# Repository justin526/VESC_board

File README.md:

# VESC_board
Our custom ESC board designed by two wonderfully inexperienced Purdue students

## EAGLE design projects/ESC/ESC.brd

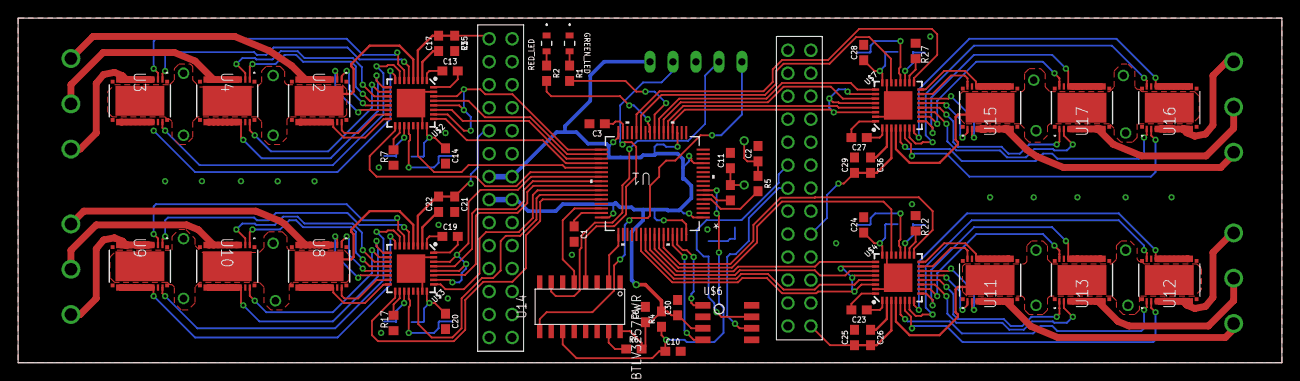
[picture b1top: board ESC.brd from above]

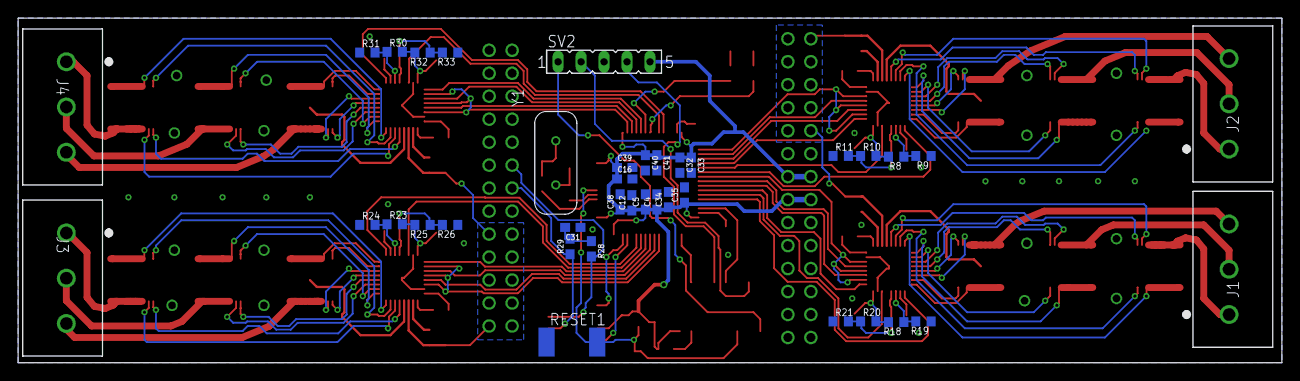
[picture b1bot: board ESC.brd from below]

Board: 4 copper layers, 139.7 x 38.1 mm, 93 parts (38 on the bottom side), 125 nets.

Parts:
C1, C3: 2.2uF; 0603
C2, C4, C5, C10, C11, C12, C16, C30, C32, C33, C34, C35, C38, C39, C40, C41: 4.7uF; 0603
C6, C15, C21, C25, C29, C31: 0.1uF; 0603
C13, C19, C23, C27: 47nF; 0603
C14, C17, C20, C22, C24, C26, C28, C36: 1.0uF; 0603
GREEN_LED: TLMS1100-GS08; LED_VISHAY_TLMX1100
J1, J2, J3, J4: 1755529; CONN_1755529
R1, R2, R3, R4, R5: 1k; 0603
R6: 1.5k; 0603
R7, R17, R22, R27: 47k; R0603
R8, R9, R10, R11, R18, R19, R20, R21, R23, R24, R25, R26, R30, R31, R32, R33: R0603
R28, R29: 60; 0603
RED_LED: TLMS1100-GS08; LED_VISHAY_TLMX1100
RESET1: SW_2512
SV2: FE05-1
U1: STM32F405RGT6; LQFP-64
U2, U3, U4, U8, U9, U10, U11, U12, U13, U15, U16, U17: CSD88584Q5DCT; DMM0022A
U14: SN74CBTLV3257PWR
U$2, U$3, U$4, U$7: DRV8320H; QFN-32-5X5MM
U$5: ESC2BACKPLANE; ESC2BACKPLANE_WHOLE
U$6: TCAN337D
Y1: ECS-80-S-4X; XTAL_ECS-80-S-4X

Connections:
+3V3: C4.1, C5.1, C6.1, C12.1, C16.1, C30.1, C32.1, C33.1, C34.1, C35.1, C38.1, C39.1, C40.1, C41.1, R4.2, R6.2, SV2.5, U1.1, U1.13, U1.19, U1.32, U1.48, U1.64, U14.P$16, U$5.P$G, U$5.P$H, U$5.P$U, U$5.P$V, U$6.VCC
+12V: C15.1, C17.2, C21.1, C22.2, C25.1, C26.2, C29.1, C36.2, U2.27, U3.27, U4.27, U8.27, U9.27, U10.27, U11.27, U12.27, U13.27, U15.27, U16.27, U17.27, U$2.3, U$2.4, U$3.3, U$3.4, U$4.3, U$4.4, U$5.P$9, U$5.P$10, U$5.P$11, U$5.P$12, U$5.P$13, U$5.P$23, U$5.P$24, U$5.P$25, U$5.P$26, U$5.P$27, U$5.P$A, U$5.P$B, U$5.P$C, U$5.P$D, U$5.P$E, U$5.P$O, U$5.P$P, U$5.P$Q, U$5.P$R, U$5.P$S, U$7.3, U$7.4
CAN_H: R28.2, U$5.P$6, U$6.CANH
CAN_L: R29.1, U$5.P$7, U$6.CANL
CAN_RX: U1.61, U$6.RXD
CAN_TX: U1.62, U$6.TXD
DVDD_1: C14.1, R8.2, R10.2, U$2.24
DVDD_2: C20.1, R18.2, R20.2, U$3.24
DVDD_3: C24.1, R23.2, R25.2, U$4.24
DVDD_4: C28.1, R30.2, R32.2, U$7.24
EN_1: U1.37, U$2.22
EN_2: U1.43, U$3.22
EN_3: U1.58, U$4.22
EN_4: U1.27, U$7.22
FAULT_1: U1.38, U$2.17
FAULT_2: U1.44, U$3.17
FAULT_3: U1.59, U$4.17
FAULT_4: U1.28, U$7.17
GHA_1: U3.1, U$2.5
GHA_2: U9.1, U$3.5
GHA_3: U12.1, U$4.5
GHA_4: U16.1, U$7.5
GHB_1: U4.1, U$2.12
GHB_2: U10.1, U$3.12
GHB_3: U13.1, U$4.12
GHB_4: U17.1, U$7.12
GHC_1: U2.1, U$2.13
GHC_2: U8.1, U$3.13
GHC_3: U11.1, U$4.13
GHC_4: U15.1, U$7.13
GLA_1: U3.22, U$2.7
GLA_2: U9.22, U$3.7
GLA_3: U12.22, U$4.7
GLA_4: U16.22, U$7.7
GLB_1: U4.22, U$2.10
GLB_2: U10.22, U$3.10
GLB_3: U13.22, U$4.10
GLB_4: U17.22, U$7.10
GLC_1: U2.22, U$2.15
GLC_2: U8.22, U$3.15
GLC_3: U11.22, U$4.15
GLC_4: U15.22, U$7.15
GND: C1.2, C2.2, C3.2, C4.2, C5.2, C6.2, C10.2, C11.2, C12.2, C14.2, C15.2, C16.2, C20.2, C21.2, C24.2, C25.2, C28.2, C29.2, C30.2, C31.1, C32.2, C33.2, C34.2, C35.2, C38.2, C39.2, C40.2, C41.2, GREEN_LED.1, R7.1, R9.1, R11.1, R17.1, R19.1, R21.1, R22.1, R24.1, R26.1, R27.1, R31.1, R33.1, RED_LED.1, RESET1.1, SV2.3, U1.12, U1.18, U1.60, U1.63, U2.12, U2.13, U2.14, U2.15, U2.16, U2.17, U2.18, U2.19, U2.20, U3.12, U3.13, U3.14, U3.15, U3.16, U3.17, U3.18, U3.19, U3.20, U4.12, U4.13, U4.14, U4.15, U4.16, U4.17, U4.18, U4.19, U4.20, U8.12, U8.13, U8.14, U8.15, U8.16, U8.17, U8.18, U8.19, U8.20, U9.12, U9.13, U9.14, U9.15, U9.16, U9.17, U9.18, U9.19, U9.20, U10.12, U10.13, U10.14, U10.15, U10.16, U10.17, U10.18, U10.19, U10.20, U11.12, U11.13, U11.14, U11.15, U11.16, U11.17, U11.18, U11.19, U11.20, U12.12, U12.13, U12.14, U12.15, U12.16, U12.17, U12.18, U12.19, U12.20, U13.12, U13.13, U13.14, U13.15, U13.16, U13.17, U13.18, U13.19, U13.20, U14.P$8, U15.12, U15.13, U15.14, U15.15, U15.16, U15.17, U15.18, U15.19, U15.20, U16.12, U16.13, U16.14, U16.15, U16.16, U16.17, U16.18, U16.19, U16.20, U17.12, U17.13, U17.14, U17.15, U17.16, U17.17, U17.18, U17.19, U17.20, U$2.8, U$2.9, U$2.16, U$2.23, U$2.31, U$2.EP, U$3.8, U$3.9, U$3.16, U$3.23, U$3.31, U$3.EP, U$4.8, U$4.9, U$4.16, U$4.23, U$4.31, U$4.EP, U$5.P$1, U$5.P$2, U$5.P$3, U$5.P$4, U$5.P$15, U$5.P$16, U$5.P$17, U$5.P$18, U$5.P$AA, U$5.P$BB, U$5.P$J, U$5.P$K, U$5.P$L, U$5.P$M, U$5.P$N, U$5.P$X, U$5.P$Y, U$5.P$Z, U$6.GND, U$7.8, U$7.9, U$7.16, U$7.23, U$7.31, U$7.EP
INHA_1: U1.36, U$2.25
INHA_2: U1.42, U$3.25
INHA_3: U1.57, U$4.25
INHA_4: U1.23, U$7.25
INHB_1: U1.35, U$2.27
INHB_2: U1.41, U$3.27
INHB_3: U1.56, U$4.27
INHB_4: U1.22, U$7.27
INHC_1: U1.34, U$2.29
INHC_2: U1.40, U$3.29
INHC_3: U1.55, U$4.29
INHC_4: U1.21, U$7.29
INL_1: U1.33, U$2.26, U$2.28, U$2.30
INL_2: U1.39, U$3.26, U$3.28, U$3.30
INL_3: U1.54, U$4.26, U$4.28, U$4.30
INL_4: U1.20, U$7.26, U$7.28, U$7.30
unnamed: R1.2, U1.24
unnamed: GREEN_LED.2, R1.1
unnamed: R2.1, RED_LED.2
unnamed: R2.2, U1.25
unnamed: C1.1, U1.47
unnamed: C3.1, U1.31
unnamed: C11.1, R3.1, Y1.2
unnamed: C2.1, R5.1, Y1.1
unnamed: C13.1, U$2.1
unnamed: R6.1, U14.P$15
unnamed: R17.2, U$3.18
unnamed: R22.2, U$4.18
unnamed: R27.2, U$7.18
unnamed: C13.2, U$2.32
unnamed: R8.1, R9.2, U$2.19
unnamed: R7.2, U$2.18
unnamed: R10.1, R11.2, U$2.20
unnamed: C22.1, U$3.2
unnamed: C19.1, U$3.1
unnamed: C19.2, U$3.32
unnamed: R18.1, R19.2, U$3.19
unnamed: R20.1, R21.2, U$3.20
unnamed: C26.1, U$4.2
unnamed: C23.1, U$4.1
unnamed: C23.2, U$4.32
unnamed: R23.1, R24.2, U$4.19
unnamed: R25.1, R26.2, U$4.20
unnamed: C36.1, U$7.2
unnamed: C17.1, U$2.2
unnamed: C27.1, U$7.1
unnamed: C27.2, U$7.32
unnamed: R30.1, R31.2, U$7.19
unnamed: R32.1, R33.2, U$7.20
unnamed: C31.2, R28.1, R29.2
NRST: C10.1, R4.1, RESET1.2, U1.7, U14.P$11
NRST_IN: SV2.1, U14.P$9
OSC_IN: R5.2, U1.5
OSC_OUT: R3.2, U1.6
PHASE_A1: J2.1, U3.3, U3.4, U3.5, U3.6, U3.7, U3.8, U3.9, U3.10, U3.11
PHASE_A2: J1.1, U9.3, U9.4, U9.5, U9.6, U9.7, U9.8, U9.9, U9.10, U9.11
PHASE_A3: J3.1, U12.3, U12.4, U12.5, U12.6, U12.7, U12.8, U12.9, U12.10, U12.11
PHASE_A4: J4.1, U16.3, U16.4, U16.5, U16.6, U16.7, U16.8, U16.9, U16.10, U16.11
PHASE_B1: J2.2, U4.3, U4.4, U4.5, U4.6, U4.7, U4.8, U4.9, U4.10, U4.11
PHASE_B2: J1.2, U10.3, U10.4, U10.5, U10.6, U10.7, U10.8, U10.9, U10.10, U10.11
PHASE_B3: J3.2, U13.3, U13.4, U13.5, U13.6, U13.7, U13.8, U13.9, U13.10, U13.11
PHASE_B4: J4.2, U17.3, U17.4, U17.5, U17.6, U17.7, U17.8, U17.9, U17.10, U17.11
PHASE_C1: J2.3, U2.3, U2.4, U2.5, U2.6, U2.7, U2.8, U2.9, U2.10, U2.11
PHASE_C2: J1.3, U8.3, U8.4, U8.5, U8.6, U8.7, U8.8, U8.9, U8.10, U8.11
PHASE_C3: J3.3, U11.3, U11.4, U11.5, U11.6, U11.7, U11.8, U11.9, U11.10, U11.11
PHASE_C4: J4.3, U15.3, U15.4, U15.5, U15.6, U15.7, U15.8, U15.9, U15.10, U15.11
SHA_1: U3.2, U$2.6
SHA_2: U9.2, U$3.6
SHA_3: U12.2, U$4.6
SHA_4: U16.2, U$7.6
SHB_1: U4.2, U$2.11
SHB_2: U10.2, U$3.11
SHB_3: U13.2, U$4.11
SHB_4: U17.2, U$7.11
SHC_1: U2.2, U$2.14
SHC_2: U8.2, U$3.14
SHC_3: U11.2, U$4.14
SHC_4: U15.2, U$7.14
SWCLK: U1.49, U14.P$2
SWCLK_IN: SV2.4, U14.P$4
SWDIO: U1.46, U14.P$5
SWDIO_IN: SV2.2, U14.P$7

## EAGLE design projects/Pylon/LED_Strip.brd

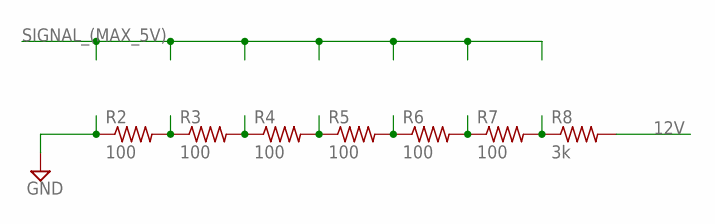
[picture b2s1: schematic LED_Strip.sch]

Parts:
R2, R3, R4, R5, R6, R7: 100; R0603
R8: 3k; R0603

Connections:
12V: R8.2
GND: R2.1
unnamed: R7.2, R8.1
unnamed: R6.2, R7.1
unnamed: R5.2, R6.1
unnamed: R4.2, R5.1
unnamed: R3.2, R4.1
unnamed: R2.2, R3.1

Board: 2 copper layers, 7 parts (0 on the bottom side), 6 nets, no tracks yet.

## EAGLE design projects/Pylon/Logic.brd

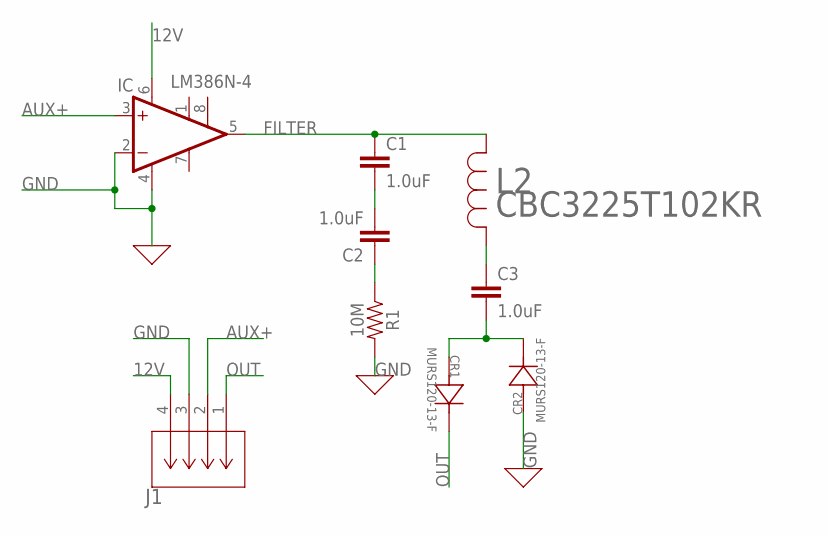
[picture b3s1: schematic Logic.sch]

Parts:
C1, C2, C3: 1.0uF; 0603
CR1, CR2: MURS120-13-F; SMB
IC: LM386N-4; DIL08
J1: SLW-104-01-T-S; CON4_1X4_TU_SLW
L2: CBC3225T102KR; IND_CBC3225T100KRV
R1: 10M; 0603

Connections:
12V: IC.6 (VS), J1.4
AUX+: IC.3 (+IN), J1.2
FILTER: C1.1, IC.5 (OUT), L2.1
GND: CR2.2, IC.2 (-IN), IC.4 (GND), J1.3, R1.2
unnamed: C2.1, R1.1
unnamed: C1.2, C2.2
unnamed: C3.2, CR1.2, CR2.1
OUT: CR1.1, J1.1
SPEAKER+: C3.1, L2.2

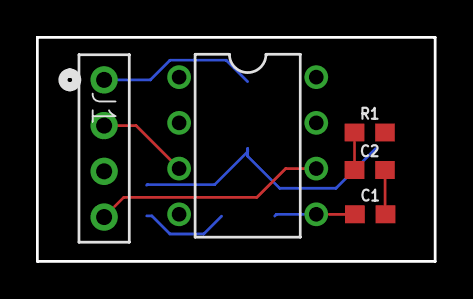
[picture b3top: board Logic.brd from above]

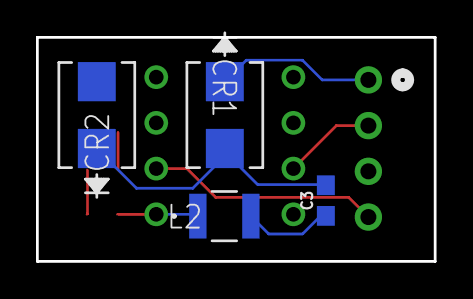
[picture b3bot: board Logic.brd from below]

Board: 2 copper layers, 22.1 x 12.4 mm, 9 parts (4 on the bottom side), 9 nets.

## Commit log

2019-06-20 github stuff
2019-06-20 Added some ICs
2019-06-20 added CAN script
2019-06-20 executed script
2019-06-20 more edits
2019-06-20 added more ICs i guess
2019-06-20 removals
2019-06-20 more additions
2019-10-02 stuff
2019-10-02 removed Pylon
2019-10-12 library updated
2019-10-19 heyyo working on my gate driver starting now
2019-10-19 finished the new gate driver
2019-10-19 ig do things l8r
2019-10-23 edits made by me
2019-10-23 took out unecessary mcu pins
2019-10-23 connectors good
2019-10-23 done with mcu
2019-10-23 stuff idk
2019-10-24 Added drv8320
2019-10-25 More Edits, new driver configured, still need IDRIVE and VDS setting
2019-10-25 Finished DRV sheets
2019-10-25 VM'd 6-packs
2019-10-25 added motor 4 to mcu, etc.
2019-10-26 changed the mcu to run on the CAN crystal, added samtec blade connectors
2019-10-26 layout of one esc
2019-10-26 made wires thicker
2019-10-26 starting motor 1 (finished motor 2)
2019-10-27 finished the left half of the board
2019-10-28 Added Fault connection from drvs to stm
    forgot to do this earlier
2019-10-28 ERC stuff 1
2019-10-29 did some layout stuff
2019-10-29 Did the right side of the board (needs polygons)
2019-11-09 fixed VM_4 trace thickness
2019-11-09 Fixed VM_3 thickness
2019-11-13 pre-meeting changes
2019-11-14 pre-review part 2
2019-11-14 no more floating polygon
2019-11-14 RIPUP MY LIFE
2019-11-16 clearing before merging
2019-11-18 Some changes have been made
2019-11-20 stuff for jonah to drc
2019-11-22 some work on the test
2019-11-22 done
2019-11-22 DRC'd version of test (now only having clearance issues)
2019-11-22 fixed(?) some stuff on the board
2019-11-22 Fixed DRC issues, sans the footprint clearance.
2019-11-22 made some changes with grant
2019-11-22 making some changes
2019-11-26 REDESIGN preliminary 1
2019-12-02 some stuff
2019-12-04 continued edits of drv setup
2019-12-06 other edits
2019-12-09 All 4 drive ckts complete
    Added and implemented design block across all 4 motors.
2019-12-16 All DRVs connected to STM
    now for the fun part...
2020-01-15 Almost finished quad ESC center
2020-01-16 Finished center of quad ESC per the schematic, multiplexer needs revisions.
    I routed the airwires, but I believe some are incorrect.
2020-01-16 Fixed center and schematics.
    "S" on the can tranciever and "S" on the multiplexer are entirely different things. and the multiplexer distinguishes between the can module and the header pin, apparently.
2020-01-16 Made naming changes to VM and SL to 12 and GND
    Changed the names for the motor voltage sources to 12 and gnd. only thing left is to connect the 12 volt supply to the 6-packs, might need another layer.
2020-01-16 Connected +12V to the motor drivers.
    Used 30 mil traces. If 3 or 4 layer board design is decided on in the future, revert to the version before this one.
2020-01-16 Revert "Connected +12V to the motor drivers."
    This reverts commit 0ece1cb6e85931862ee2ef5365700be815a9b472.
2020-01-17 Added 2 layers and made some polygons for +12V
2020-01-22 Finished test board (before ratsnest)
2020-01-22 finished test board (after ratsnest and a few tweaks)
2020-01-23 Quad ESC tidying up
2020-01-23 More tidying up
2020-01-23 took off 12v thermals
2020-01-23 Ratsnested, grounded things
2020-01-23 Fixed all of the simple errors

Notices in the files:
parts and their libraries:
SparkFun-Capacitors: Licensing: Creative Commons ShareAlike 4.0 International - https://creativecommons.org/licenses/by-sa/4.0
